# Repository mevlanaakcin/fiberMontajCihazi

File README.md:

# fiberMontajCihazi
Uçak Elektronik sanayisinde fiberoptik kabloların soketlenmesi için geliştirilen cihaz<br>
<h3>PCB Tasarımı</h3><br>
Elektronik devre şeması ve PCB board tasarımı Eagle de tasarlandı.<br>

<h3>Gömülü Yazılım</h3><br>
Bir masaüstü haberleşme ile iletişim kurabilmesi için Serial Haberleşme kullanıldı.<br>
LCD ekran için I2C kullanıldı.<br>
Shift Register Entegrelerini sürebilmek için SPI kullanıldı.<br>

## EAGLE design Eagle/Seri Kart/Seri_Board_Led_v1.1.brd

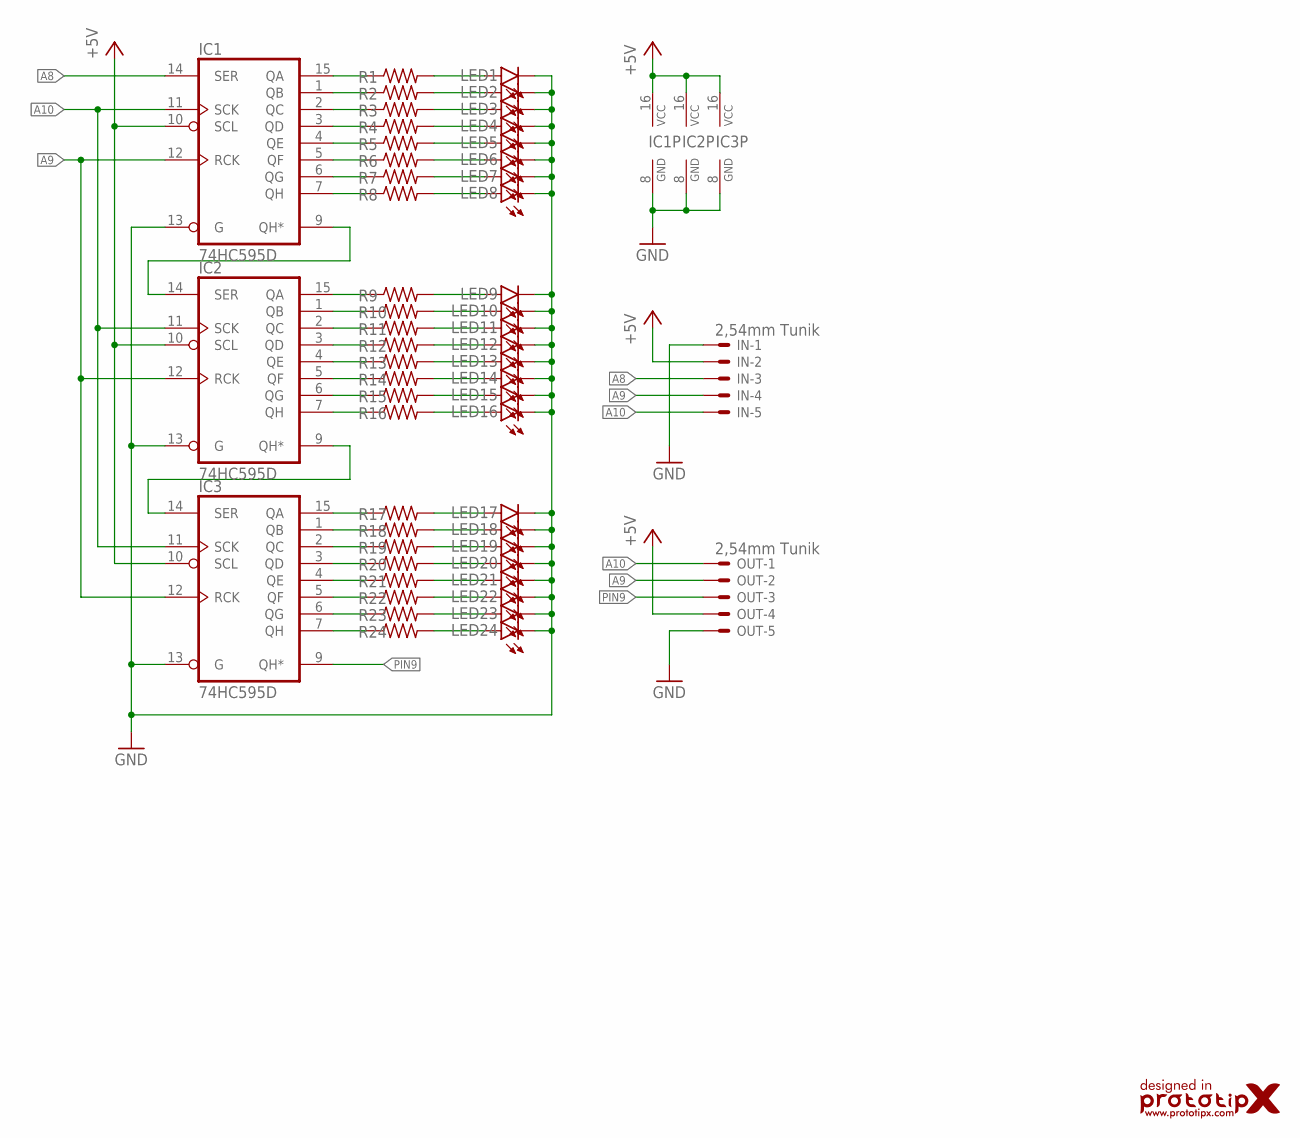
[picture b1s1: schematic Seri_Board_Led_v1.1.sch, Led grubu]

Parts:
IC1, IC2, IC3: 74HC595D; SO16
IN: 2,54mm Tunik; 70543-05
LED1, LED2, LED3, LED4, LED5, LED6, LED7, LED8, LED9, LED10, LED11, LED12, LED13, LED14, LED15, LED16, LED17, LED18, LED19, LED20, LED21, LED22, LED23, LED24: RED; LED3MM
LOGO1: PROTOTIPXDESIGN2; PROTOTIPX_DESING_15MM
OUT: 2,54mm Tunik; 70543-05
R1, R2, R3, R4, R5, R6, R7, R8, R9, R10, R11, R12, R13, R14, R15, R16, R17, R18, R19, R20, R21, R22, R23, R24: 220R; R0805

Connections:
+5V: IC1.10 (SCL), IC1.16 (VCC), IC2.10 (SCL), IC2.16 (VCC), IC3.10 (SCL), IC3.16 (VCC), IN.2, OUT.4
A8: IC1.14 (SER), IN.3
A9: IC1.12 (RCK), IC2.12 (RCK), IC3.12 (RCK), IN.4, OUT.2
A10: IC1.11 (SCK), IC2.11 (SCK), IC3.11 (SCK), IN.5, OUT.1
GND: IC1.8 (GND), IC1.13 (G), IC2.8 (GND), IC2.13 (G), IC3.8 (GND), IC3.13 (G), IN.1, LED1.K (C), LED2.K (C), LED3.K (C), LED4.K (C), LED5.K (C), LED6.K (C), LED7.K (C), LED8.K (C), LED9.K (C), LED10.K (C), LED11.K (C), LED12.K (C), LED13.K (C), LED14.K (C), LED15.K (C), LED16.K (C), LED17.K (C), LED18.K (C), LED19.K (C), LED20.K (C), LED21.K (C), LED22.K (C), LED23.K (C), LED24.K (C), OUT.5
unnamed: LED1.A, R1.2
unnamed: IC1.15 (QA), R1.1
unnamed: IC1.1 (QB), R2.1
unnamed: LED2.A, R2.2
unnamed: IC1.2 (QC), R3.1
unnamed: LED3.A, R3.2
unnamed: IC1.3 (QD), R4.1
unnamed: LED4.A, R4.2
unnamed: IC1.4 (QE), R5.1
unnamed: LED5.A, R5.2
unnamed: IC1.5 (QF), R6.1
unnamed: LED6.A, R6.2
unnamed: IC1.6 (QG), R7.1
unnamed: LED7.A, R7.2
unnamed: IC1.7 (QH), R8.1
unnamed: LED8.A, R8.2
unnamed: IC2.15 (QA), R9.1
unnamed: LED9.A, R9.2
unnamed: IC2.1 (QB), R10.1
unnamed: LED10.A, R10.2
unnamed: IC2.2 (QC), R11.1
unnamed: LED11.A, R11.2
unnamed: IC2.3 (QD), R12.1
unnamed: LED12.A, R12.2
unnamed: IC2.4 (QE), R13.1
unnamed: LED13.A, R13.2
unnamed: IC2.5 (QF), R14.1
unnamed: LED14.A, R14.2
unnamed: IC2.6 (QG), R15.1
unnamed: LED15.A, R15.2
unnamed: IC2.7 (QH), R16.1
unnamed: LED16.A, R16.2
unnamed: IC3.15 (QA), R17.1
unnamed: LED17.A, R17.2
unnamed: IC3.1 (QB), R18.1
unnamed: LED18.A, R18.2
unnamed: IC3.2 (QC), R19.1
unnamed: LED19.A, R19.2
unnamed: IC3.3 (QD), R20.1
unnamed: LED20.A, R20.2
unnamed: IC3.4 (QE), R21.1
unnamed: LED21.A, R21.2
unnamed: IC3.5 (QF), R22.1
unnamed: LED22.A, R22.2
unnamed: IC3.6 (QG), R23.1
unnamed: LED23.A, R23.2
unnamed: IC3.7 (QH), R24.1
unnamed: LED24.A, R24.2
unnamed: IC1.9 (QH*), IC2.14 (SER)
unnamed: IC2.9 (QH*), IC3.14 (SER)
PIN9: IC3.9 (QH*), OUT.3

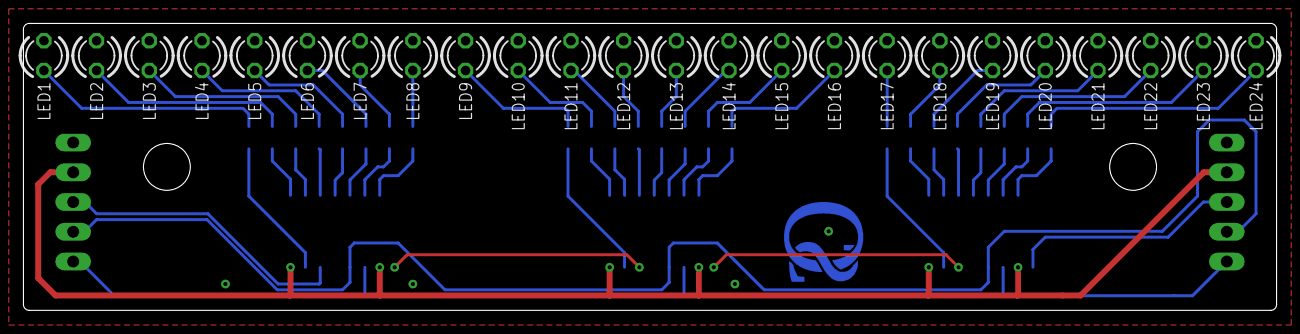
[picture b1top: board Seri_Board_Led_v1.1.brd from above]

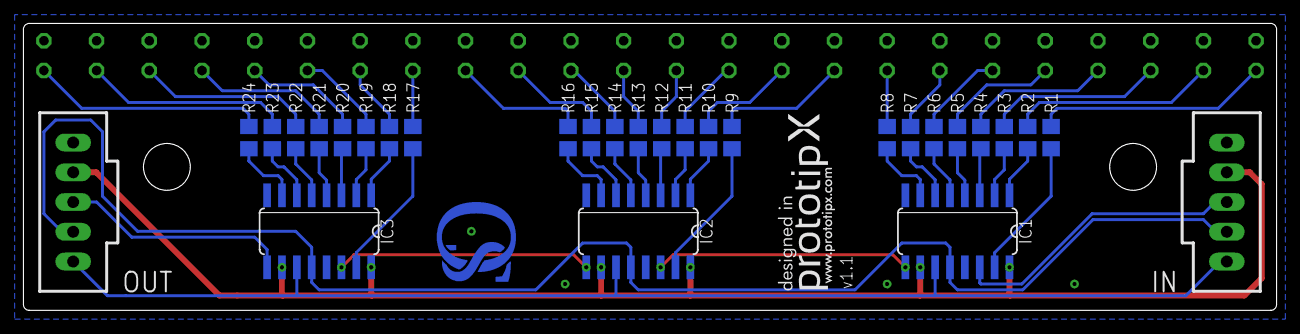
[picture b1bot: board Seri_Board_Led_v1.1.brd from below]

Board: 2 copper layers, 107.0 x 24.5 mm, 54 parts (30 on the bottom side), 56 nets.

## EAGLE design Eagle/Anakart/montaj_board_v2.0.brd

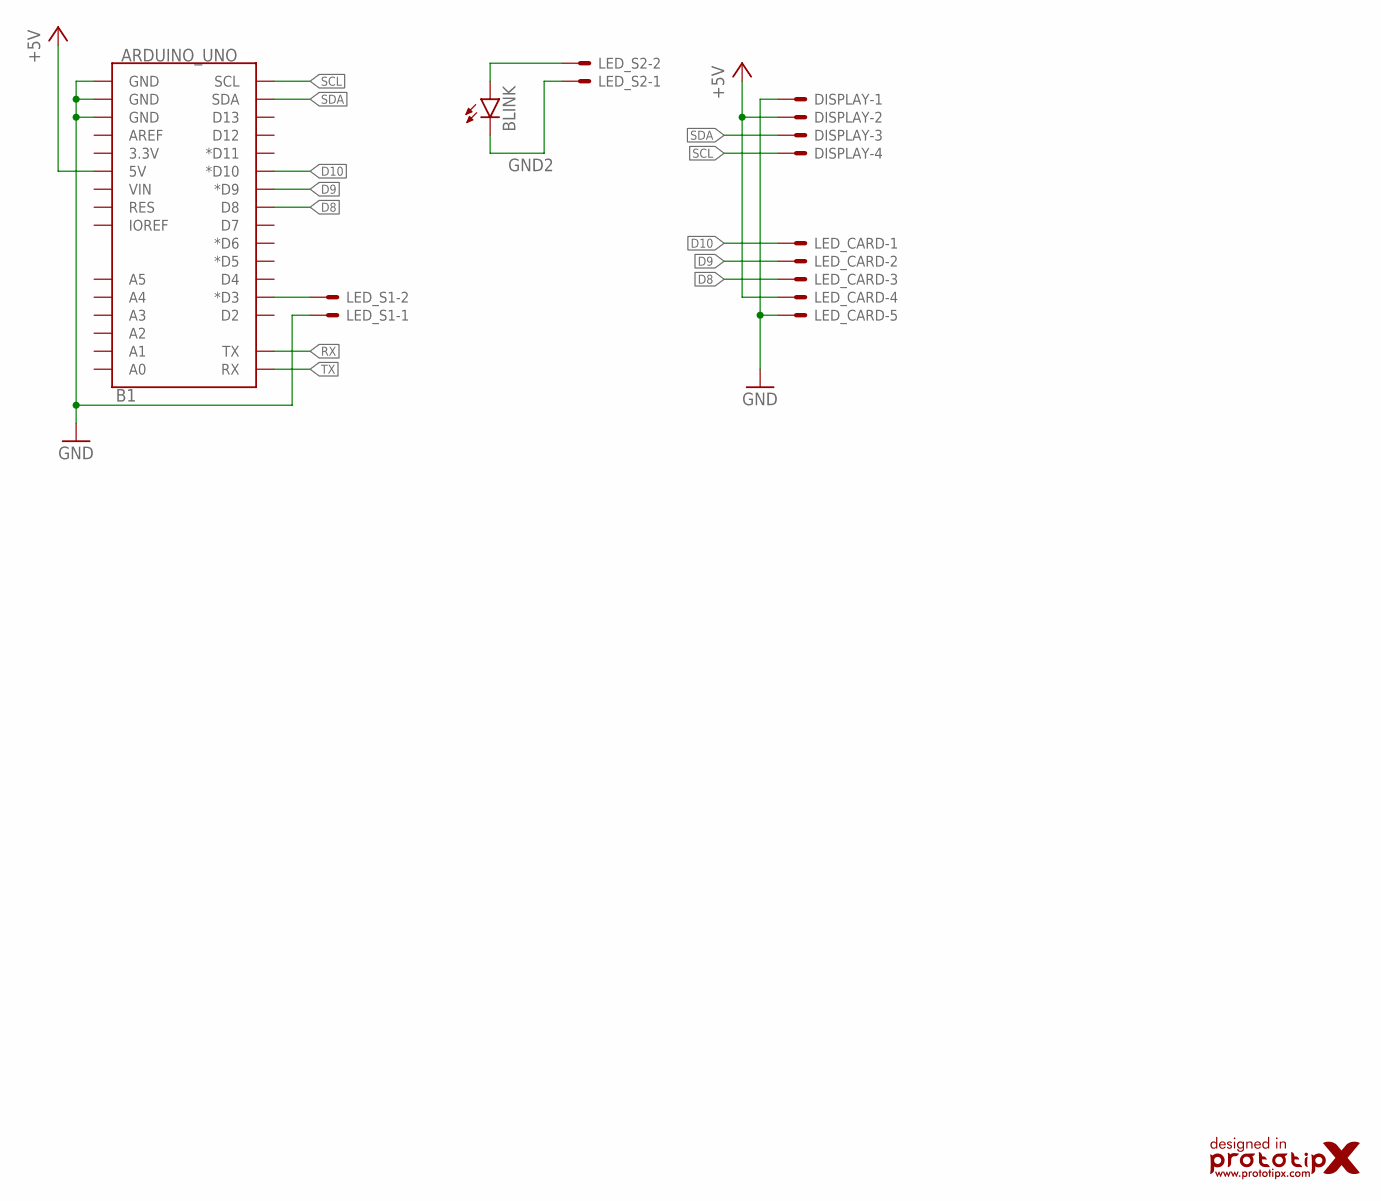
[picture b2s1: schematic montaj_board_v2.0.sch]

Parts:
B1: ARDUINO_UNO; UNO_R3_SHIELD
BLINK: LED3MM
DISPLAY: C-GRID-04-70543; 70543-04
LED_CARD: C-GRID-05-70543; 70543-05
LED_S1, LED_S2: C-GRID-02-70543; 70543-02
LOGO1: PROTOTIPXDESIGN; PROTOTIPX_DESING_20MM

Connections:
+5V: B1.5V, DISPLAY.2, LED_CARD.4
D8: B1.D8, LED_CARD.3
D9: B1.D9 (*D9), LED_CARD.2
D10: B1.D10 (*D10), LED_CARD.1
GND: B1.GND@0 (GND), B1.GND@1 (GND), B1.GND@2 (GND), DISPLAY.1, LED_CARD.5, LED_S1.1
GND2: BLINK.K (C), LED_S2.1
unnamed: B1.D3 (*D3), LED_S1.2
unnamed: BLINK.A, LED_S2.2
RX: B1.TX
SCL: B1.SCL, DISPLAY.4
SDA: B1.SDA, DISPLAY.3
TX: B1.RX

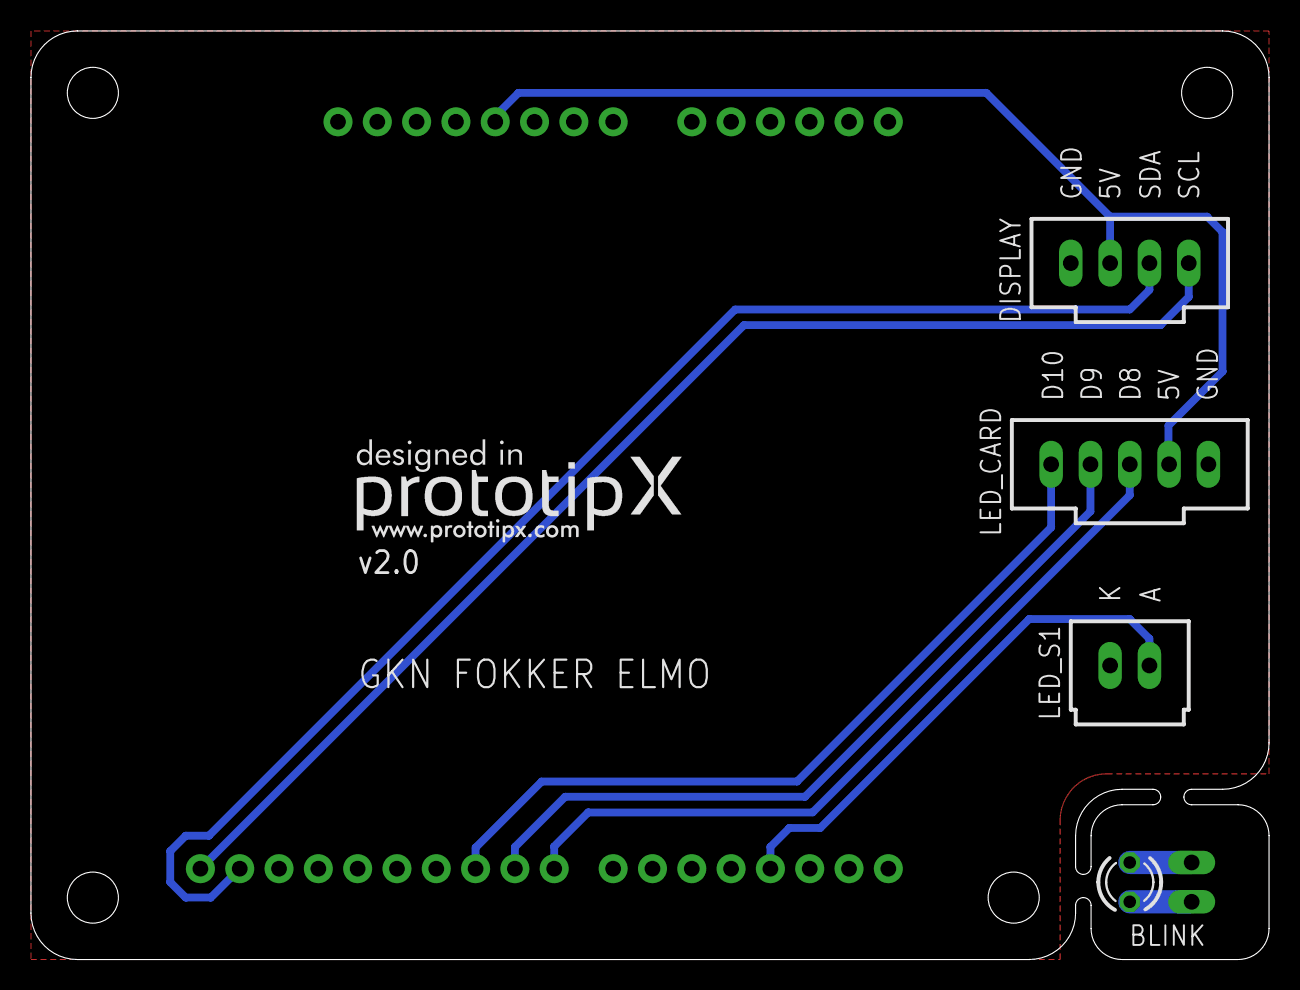
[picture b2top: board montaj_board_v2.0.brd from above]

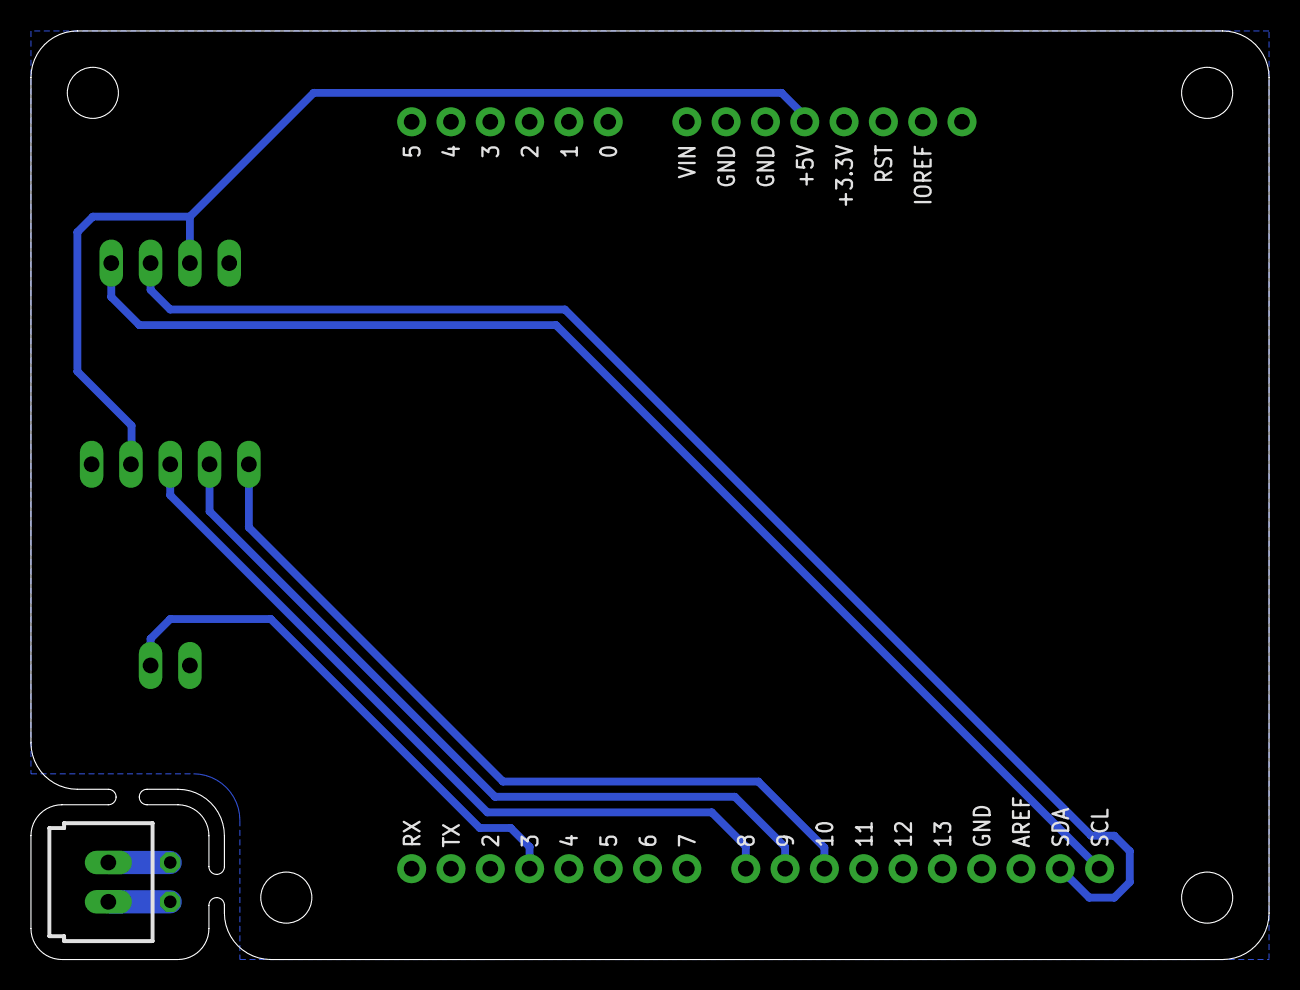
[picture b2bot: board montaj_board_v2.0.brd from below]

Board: 2 copper layers, 80.0 x 60.0 mm, 7 parts (2 on the bottom side), 10 nets.

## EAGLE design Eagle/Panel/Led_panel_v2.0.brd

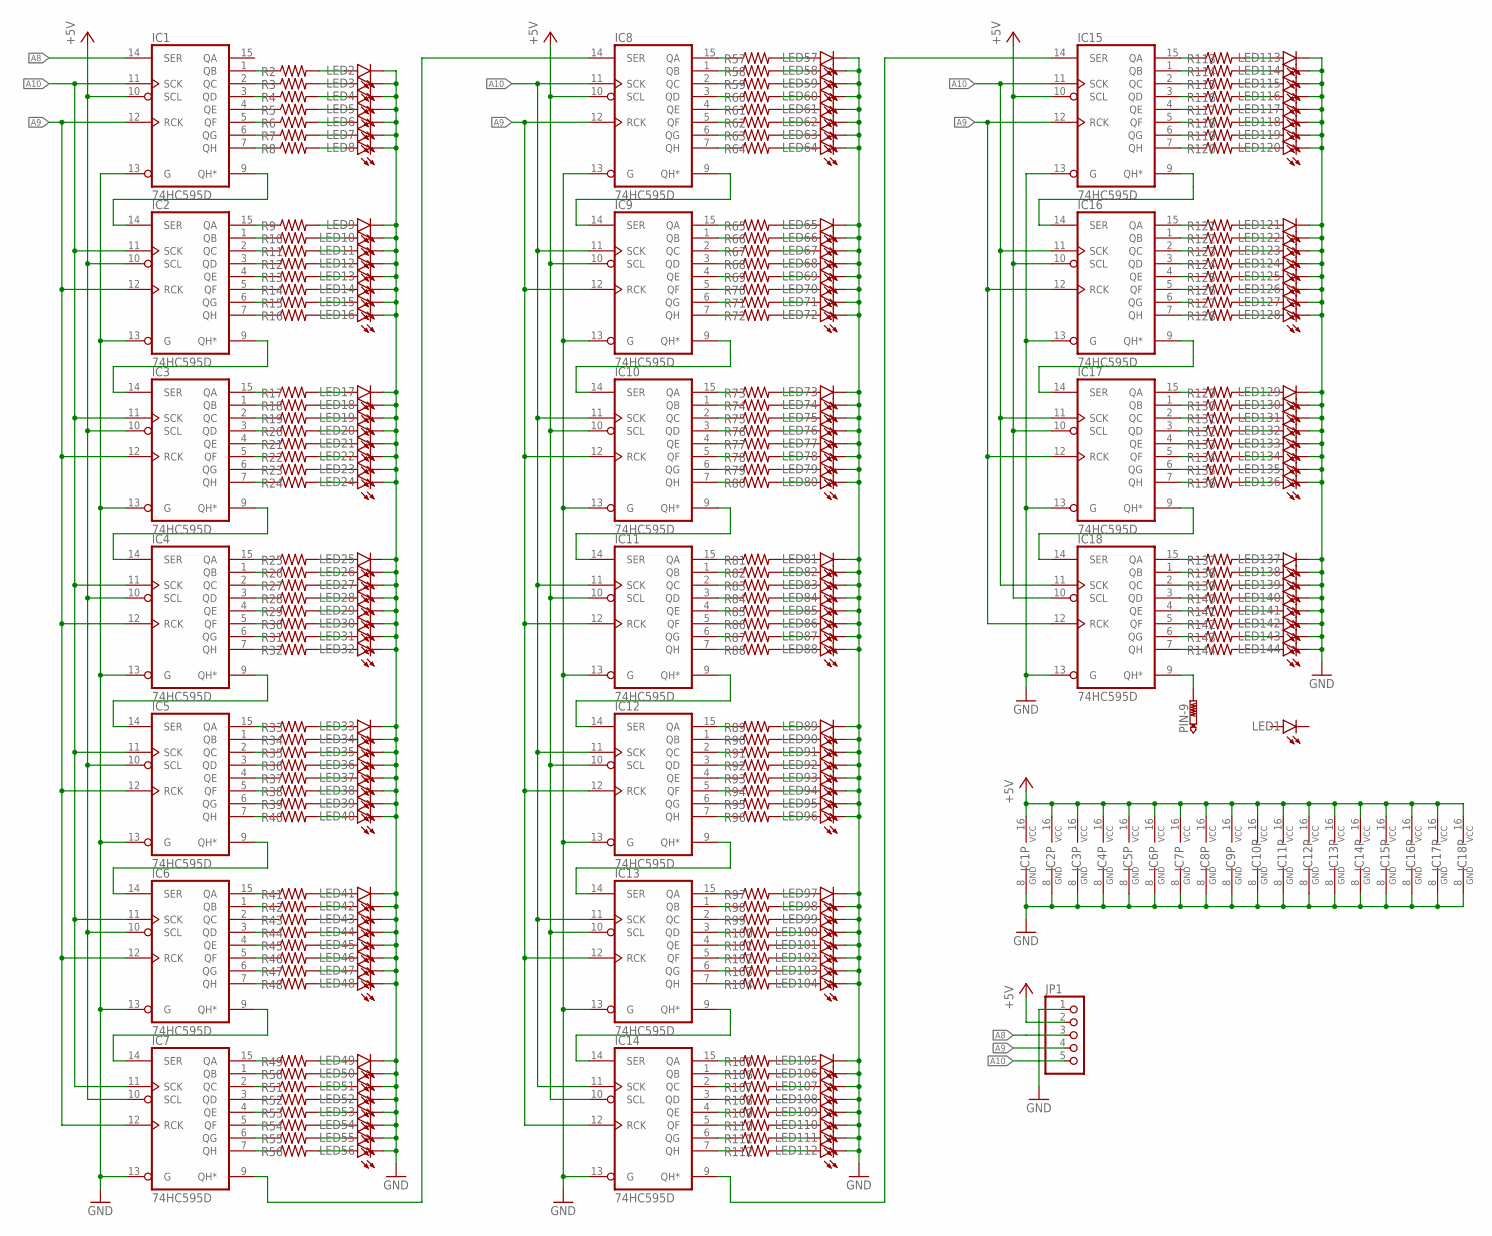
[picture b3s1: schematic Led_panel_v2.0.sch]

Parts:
IC1, IC2, IC3, IC4, IC5, IC6, IC7, IC8, IC9, IC10, IC11, IC12, IC13, IC14, IC15, IC16, IC17, IC18: 74HC595D; SO16
JP1: PINHD-1X5; 1X05
LED1, LED2, LED3, LED4, LED5, LED6, LED7, LED8, LED9, LED10, LED11, LED12, LED13, LED14, LED15, LED16, LED17, LED18, LED19, LED20, LED21, LED22, LED23, LED24, LED25, LED26, LED27, LED28, LED29, LED30, LED31, LED32, LED33, LED34, LED35, LED36, LED37, LED38, LED39, LED40, LED41, LED42, LED43, LED44, LED45, LED46, LED47, LED48, LED49, LED50, LED51, LED52, LED53, LED54, LED55, LED56, LED57, LED58, LED59, LED60, LED61, LED62, LED63, LED64, LED65, LED66, LED67, LED68, LED69, LED70, LED71, LED72, LED73, LED74, LED75, LED76, LED77, LED78, LED79, LED80, LED81, LED82, LED83, LED84, LED85, LED86, LED87, LED88, LED89, LED90, LED91, LED92, LED93, LED94, LED95, LED96, LED97, LED98, LED99, LED100, LED101, LED102, LED103, LED104, LED105, LED106, LED107, LED108, LED109, LED110, LED111, LED112, LED113, LED114, LED115, LED116, LED117, LED118, LED119, LED120, LED121, LED122, LED123, LED124, LED125, LED126, LED127, LED128, LED129, LED130, LED131, LED132, LED133, LED134, LED135, LED136, LED137, LED138, LED139, LED140, LED141, LED142, LED143, LED144: LED3MM
PIN-9: PTR1TP20R; TP20R
R2, R3, R4, R5, R6, R7, R8, R9, R10, R11, R12, R13, R14, R15, R16, R17, R18, R19, R20, R21, R22, R23, R24, R25, R26, R27, R28, R29, R30, R31, R32, R33, R34, R35, R36, R37, R38, R39, R40, R41, R42, R43, R44, R45, R46, R47, R48, R49, R50, R51, R52, R53, R54, R55, R56, R57, R58, R59, R60, R61, R62, R63, R64, R65, R66, R67, R68, R69, R70, R71, R72, R73, R74, R75, R76, R77, R78, R79, R80, R81, R82, R83, R84, R85, R86, R87, R88, R89, R90, R91, R92, R93, R94, R95, R96, R97, R98, R99, R100, R101, R102, R103, R104, R105, R106, R107, R108, R109, R110, R111, R112, R113, R114, R115, R116, R117, R118, R119, R120, R121, R122, R123, R124, R125, R126, R127, R128, R129, R130, R131, R132, R133, R134, R135, R136, R137, R138, R139, R140, R141, R142, R143, R144: 120R; R0805

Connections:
+5V: IC1.10 (SCL), IC1.16 (VCC), IC2.10 (SCL), IC2.16 (VCC), IC3.10 (SCL), IC3.16 (VCC), IC4.10 (SCL), IC4.16 (VCC), IC5.10 (SCL), IC5.16 (VCC), IC6.10 (SCL), IC6.16 (VCC), IC7.10 (SCL), IC7.16 (VCC), IC8.10 (SCL), IC8.16 (VCC), IC9.10 (SCL), IC9.16 (VCC), IC10.10 (SCL), IC10.16 (VCC), IC11.10 (SCL), IC11.16 (VCC), IC12.10 (SCL), IC12.16 (VCC), IC13.10 (SCL), IC13.16 (VCC), IC14.10 (SCL), IC14.16 (VCC), IC15.10 (SCL), IC15.16 (VCC), IC16.10 (SCL), IC16.16 (VCC), IC17.10 (SCL), IC17.16 (VCC), IC18.10 (SCL), IC18.16 (VCC), JP1.2
A8: IC1.14 (SER), JP1.3
A9: IC1.12 (RCK), IC2.12 (RCK), IC3.12 (RCK), IC4.12 (RCK), IC5.12 (RCK), IC6.12 (RCK), IC7.12 (RCK), IC8.12 (RCK), IC9.12 (RCK), IC10.12 (RCK), IC11.12 (RCK), IC12.12 (RCK), IC13.12 (RCK), IC14.12 (RCK), IC15.12 (RCK), IC16.12 (RCK), IC17.12 (RCK), IC18.12 (RCK), JP1.4
A10: IC1.11 (SCK), IC2.11 (SCK), IC3.11 (SCK), IC4.11 (SCK), IC5.11 (SCK), IC6.11 (SCK), IC7.11 (SCK), IC8.11 (SCK), IC9.11 (SCK), IC10.11 (SCK), IC11.11 (SCK), IC12.11 (SCK), IC13.11 (SCK), IC14.11 (SCK), IC15.11 (SCK), IC16.11 (SCK), IC17.11 (SCK), IC18.11 (SCK), JP1.5
GND: IC1.8 (GND), IC1.13 (G), IC2.8 (GND), IC2.13 (G), IC3.8 (GND), IC3.13 (G), IC4.8 (GND), IC4.13 (G), IC5.8 (GND), IC5.13 (G), IC6.8 (GND), IC6.13 (G), IC7.8 (GND), IC7.13 (G), IC8.8 (GND), IC8.13 (G), IC9.8 (GND), IC9.13 (G), IC10.8 (GND), IC10.13 (G), IC11.8 (GND), IC11.13 (G), IC12.8 (GND), IC12.13 (G), IC13.8 (GND), IC13.13 (G), IC14.8 (GND), IC14.13 (G), IC15.8 (GND), IC15.13 (G), IC16.8 (GND), IC16.13 (G), IC17.8 (GND), IC17.13 (G), IC18.8 (GND), IC18.13 (G), JP1.1, LED2.K (C), LED3.K (C), LED4.K (C), LED5.K (C), LED6.K (C), LED7.K (C), LED8.K (C), LED9.K (C), LED10.K (C), LED11.K (C), LED12.K (C), LED13.K (C), LED14.K (C), LED15.K (C), LED16.K (C), LED17.K (C), LED18.K (C), LED19.K (C), LED20.K (C), LED21.K (C), LED22.K (C), LED23.K (C), LED24.K (C), LED25.K (C), LED26.K (C), LED27.K (C), LED28.K (C), LED29.K (C), LED30.K (C), LED31.K (C), LED32.K (C), LED33.K (C), LED34.K (C), LED35.K (C), LED36.K (C), LED37.K (C), LED38.K (C), LED39.K (C), LED40.K (C), LED41.K (C), LED42.K (C), LED43.K (C), LED44.K (C), LED45.K (C), LED46.K (C), LED47.K (C), LED48.K (C), LED49.K (C), LED50.K (C), LED51.K (C), LED52.K (C), LED53.K (C), LED54.K (C), LED55.K (C), LED56.K (C), LED57.K (C), LED58.K (C), LED59.K (C), LED60.K (C), LED61.K (C), LED62.K (C), LED63.K (C), LED64.K (C), LED65.K (C), LED66.K (C), LED67.K (C), LED68.K (C), LED69.K (C), LED70.K (C), LED71.K (C), LED72.K (C), LED73.K (C), LED74.K (C), LED75.K (C), LED76.K (C), LED77.K (C), LED78.K (C), LED79.K (C), LED80.K (C), LED81.K (C), LED82.K (C), LED83.K (C), LED84.K (C), LED85.K (C), LED86.K (C), LED87.K (C), LED88.K (C), LED89.K (C), LED90.K (C), LED91.K (C), LED92.K (C), LED93.K (C), LED94.K (C), LED95.K (C), LED96.K (C), LED97.K (C), LED98.K (C), LED99.K (C), LED100.K (C), LED101.K (C), LED102.K (C), LED103.K (C), LED104.K (C), LED105.K (C), LED106.K (C), LED107.K (C), LED108.K (C), LED109.K (C), LED110.K (C), LED111.K (C), LED112.K (C), LED113.K (C), LED114.K (C), LED115.K (C), LED116.K (C), LED117.K (C), LED118.K (C), LED119.K (C), LED120.K (C), LED121.K (C), LED122.K (C), LED123.K (C), LED124.K (C), LED125.K (C), LED126.K (C), LED127.K (C), LED128.K (C), LED129.K (C), LED130.K (C), LED131.K (C), LED132.K (C), LED133.K (C), LED134.K (C), LED135.K (C), LED136.K (C), LED137.K (C), LED138.K (C), LED139.K (C), LED140.K (C), LED141.K (C), LED142.K (C), LED143.K (C), LED144.K (C)
unnamed: IC18.9 (QH*), PIN-9.TP
unnamed: IC1.1 (QB), R2.1
unnamed: LED2.A, R2.2
unnamed: IC1.2 (QC), R3.1
unnamed: LED3.A, R3.2
unnamed: IC1.3 (QD), R4.1
unnamed: LED4.A, R4.2
unnamed: IC1.4 (QE), R5.1
unnamed: LED5.A, R5.2
unnamed: IC1.5 (QF), R6.1
unnamed: LED6.A, R6.2
unnamed: IC1.6 (QG), R7.1
unnamed: LED7.A, R7.2
unnamed: IC1.7 (QH), R8.1
unnamed: LED8.A, R8.2
unnamed: IC2.15 (QA), R9.1
unnamed: LED9.A, R9.2
unnamed: IC2.1 (QB), R10.1
unnamed: LED10.A, R10.2
unnamed: IC2.2 (QC), R11.1
unnamed: LED11.A, R11.2
unnamed: IC2.3 (QD), R12.1
unnamed: LED12.A, R12.2
unnamed: IC2.4 (QE), R13.1
unnamed: LED13.A, R13.2
unnamed: IC2.5 (QF), R14.1
unnamed: LED14.A, R14.2
unnamed: IC2.6 (QG), R15.1
unnamed: LED15.A, R15.2
unnamed: IC2.7 (QH), R16.1
unnamed: LED16.A, R16.2
unnamed: IC3.15 (QA), R17.1
unnamed: LED17.A, R17.2
unnamed: IC3.1 (QB), R18.1
unnamed: LED18.A, R18.2
unnamed: IC3.2 (QC), R19.1
unnamed: LED19.A, R19.2
unnamed: IC3.3 (QD), R20.1
unnamed: LED20.A, R20.2
unnamed: IC3.4 (QE), R21.1
unnamed: LED21.A, R21.2
unnamed: IC3.5 (QF), R22.1
unnamed: LED22.A, R22.2
unnamed: IC3.6 (QG), R23.1
unnamed: LED23.A, R23.2
unnamed: IC3.7 (QH), R24.1
unnamed: LED24.A, R24.2
unnamed: IC4.15 (QA), R25.1
unnamed: LED25.A, R25.2
unnamed: IC4.1 (QB), R26.1
unnamed: LED26.A, R26.2
unnamed: IC4.2 (QC), R27.1
unnamed: LED27.A, R27.2
unnamed: IC4.3 (QD), R28.1
unnamed: LED28.A, R28.2
unnamed: IC4.4 (QE), R29.1
unnamed: LED29.A, R29.2
unnamed: IC4.5 (QF), R30.1
unnamed: LED30.A, R30.2
unnamed: IC4.6 (QG), R31.1
unnamed: LED31.A, R31.2
unnamed: IC4.7 (QH), R32.1
unnamed: LED32.A, R32.2
unnamed: IC5.15 (QA), R33.1
unnamed: LED33.A, R33.2
unnamed: IC5.1 (QB), R34.1
unnamed: LED34.A, R34.2
unnamed: IC5.2 (QC), R35.1
unnamed: LED35.A, R35.2
unnamed: IC5.3 (QD), R36.1
unnamed: LED36.A, R36.2
unnamed: IC5.4 (QE), R37.1
unnamed: LED37.A, R37.2
unnamed: IC5.5 (QF), R38.1
unnamed: LED38.A, R38.2
unnamed: IC5.6 (QG), R39.1
unnamed: LED39.A, R39.2
unnamed: IC5.7 (QH), R40.1
unnamed: LED40.A, R40.2
unnamed: IC6.15 (QA), R41.1
unnamed: LED41.A, R41.2
unnamed: IC6.1 (QB), R42.1
unnamed: LED42.A, R42.2
unnamed: IC6.2 (QC), R43.1
unnamed: LED43.A, R43.2
unnamed: IC6.3 (QD), R44.1
unnamed: LED44.A, R44.2
unnamed: IC6.4 (QE), R45.1
unnamed: LED45.A, R45.2
unnamed: IC6.5 (QF), R46.1
unnamed: LED46.A, R46.2
unnamed: IC6.6 (QG), R47.1
unnamed: LED47.A, R47.2
unnamed: IC6.7 (QH), R48.1
unnamed: LED48.A, R48.2
unnamed: IC7.15 (QA), R49.1
unnamed: LED49.A, R49.2
unnamed: IC7.1 (QB), R50.1
unnamed: LED50.A, R50.2
unnamed: IC7.2 (QC), R51.1
unnamed: LED51.A, R51.2
unnamed: IC7.3 (QD), R52.1
unnamed: LED52.A, R52.2
unnamed: IC7.4 (QE), R53.1
unnamed: LED53.A, R53.2
unnamed: IC7.5 (QF), R54.1
unnamed: LED54.A, R54.2
unnamed: IC7.6 (QG), R55.1
unnamed: LED55.A, R55.2
unnamed: IC7.7 (QH), R56.1
unnamed: LED56.A, R56.2
unnamed: IC8.15 (QA), R57.1
unnamed: LED57.A, R57.2
unnamed: IC8.1 (QB), R58.1
unnamed: LED58.A, R58.2
unnamed: IC8.2 (QC), R59.1
unnamed: LED59.A, R59.2
unnamed: IC8.3 (QD), R60.1
unnamed: LED60.A, R60.2
unnamed: IC8.4 (QE), R61.1
unnamed: LED61.A, R61.2
unnamed: IC8.5 (QF), R62.1
unnamed: LED62.A, R62.2
unnamed: IC8.6 (QG), R63.1
unnamed: LED63.A, R63.2
unnamed: IC8.7 (QH), R64.1
unnamed: LED64.A, R64.2
unnamed: IC9.15 (QA), R65.1
unnamed: LED65.A, R65.2
unnamed: IC9.1 (QB), R66.1
unnamed: LED66.A, R66.2
unnamed: IC9.2 (QC), R67.1
unnamed: LED67.A, R67.2
unnamed: IC9.3 (QD), R68.1
unnamed: LED68.A, R68.2
unnamed: IC9.4 (QE), R69.1
unnamed: LED69.A, R69.2
unnamed: IC9.5 (QF), R70.1
unnamed: LED70.A, R70.2
unnamed: IC9.6 (QG), R71.1
unnamed: LED71.A, R71.2
unnamed: IC9.7 (QH), R72.1
unnamed: LED72.A, R72.2
unnamed: IC10.15 (QA), R73.1
unnamed: LED73.A, R73.2
unnamed: IC10.1 (QB), R74.1
unnamed: LED74.A, R74.2
unnamed: IC10.2 (QC), R75.1
unnamed: LED75.A, R75.2
unnamed: IC10.3 (QD), R76.1
unnamed: LED76.A, R76.2
unnamed: IC10.4 (QE), R77.1
unnamed: LED77.A, R77.2
unnamed: IC10.5 (QF), R78.1
unnamed: LED78.A, R78.2
unnamed: IC10.6 (QG), R79.1
unnamed: LED79.A, R79.2
unnamed: IC10.7 (QH), R80.1
unnamed: LED80.A, R80.2
unnamed: IC11.15 (QA), R81.1
unnamed: LED81.A, R81.2
unnamed: IC11.1 (QB), R82.1
unnamed: LED82.A, R82.2
unnamed: IC11.2 (QC), R83.1
unnamed: LED83.A, R83.2
unnamed: IC11.3 (QD), R84.1
unnamed: LED84.A, R84.2
unnamed: IC11.4 (QE), R85.1
unnamed: LED85.A, R85.2
unnamed: IC11.5 (QF), R86.1
unnamed: LED86.A, R86.2
unnamed: IC11.6 (QG), R87.1
unnamed: LED87.A, R87.2
unnamed: IC11.7 (QH), R88.1
unnamed: LED88.A, R88.2
unnamed: IC12.15 (QA), R89.1
unnamed: LED89.A, R89.2
unnamed: IC12.1 (QB), R90.1
unnamed: LED90.A, R90.2
unnamed: IC12.2 (QC), R91.1
unnamed: LED91.A, R91.2
unnamed: IC12.3 (QD), R92.1
unnamed: LED92.A, R92.2
unnamed: IC12.4 (QE), R93.1
unnamed: LED93.A, R93.2
unnamed: IC12.5 (QF), R94.1
unnamed: LED94.A, R94.2
unnamed: IC12.6 (QG), R95.1
unnamed: LED95.A, R95.2
unnamed: IC12.7 (QH), R96.1
unnamed: LED96.A, R96.2
unnamed: IC13.15 (QA), R97.1
unnamed: LED97.A, R97.2
unnamed: IC13.1 (QB), R98.1
unnamed: LED98.A, R98.2
unnamed: IC13.2 (QC), R99.1
unnamed: LED99.A, R99.2
unnamed: IC13.3 (QD), R100.1
unnamed: LED100.A, R100.2
unnamed: IC13.4 (QE), R101.1
unnamed: LED101.A, R101.2
unnamed: IC13.5 (QF), R102.1
unnamed: LED102.A, R102.2
unnamed: IC13.6 (QG), R103.1
unnamed: LED103.A, R103.2
unnamed: IC13.7 (QH), R104.1
unnamed: LED104.A, R104.2
unnamed: IC14.15 (QA), R105.1
unnamed: LED105.A, R105.2
unnamed: IC14.1 (QB), R106.1
unnamed: LED106.A, R106.2
unnamed: IC14.2 (QC), R107.1
unnamed: LED107.A, R107.2
unnamed: IC14.3 (QD), R108.1
unnamed: LED108.A, R108.2
unnamed: IC14.4 (QE), R109.1
unnamed: LED109.A, R109.2
unnamed: IC14.5 (QF), R110.1
unnamed: LED110.A, R110.2
unnamed: IC14.6 (QG), R111.1
unnamed: LED111.A, R111.2
unnamed: IC14.7 (QH), R112.1
unnamed: LED112.A, R112.2
unnamed: IC15.15 (QA), R113.1
unnamed: LED113.A, R113.2
unnamed: IC15.1 (QB), R114.1
unnamed: LED114.A, R114.2
unnamed: IC15.2 (QC), R115.1
unnamed: LED115.A, R115.2
unnamed: IC15.3 (QD), R116.1
unnamed: LED116.A, R116.2
unnamed: IC15.4 (QE), R117.1
unnamed: LED117.A, R117.2
unnamed: IC15.5 (QF), R118.1
unnamed: LED118.A, R118.2
unnamed: IC15.6 (QG), R119.1
unnamed: LED119.A, R119.2
unnamed: IC15.7 (QH), R120.1
unnamed: LED120.A, R120.2
unnamed: IC16.15 (QA), R121.1
unnamed: LED121.A, R121.2
unnamed: IC16.1 (QB), R122.1
unnamed: LED122.A, R122.2
unnamed: IC16.2 (QC), R123.1
unnamed: LED123.A, R123.2
unnamed: IC16.3 (QD), R124.1
unnamed: LED124.A, R124.2
unnamed: IC16.4 (QE), R125.1
unnamed: LED125.A, R125.2
unnamed: IC16.5 (QF), R126.1
unnamed: LED126.A, R126.2
unnamed: IC16.6 (QG), R127.1
unnamed: LED127.A, R127.2
unnamed: IC16.7 (QH), R128.1
unnamed: LED128.A, R128.2
unnamed: IC17.15 (QA), R129.1
unnamed: LED129.A, R129.2
unnamed: IC17.1 (QB), R130.1
unnamed: LED130.A, R130.2
unnamed: IC17.2 (QC), R131.1
unnamed: LED131.A, R131.2
unnamed: IC17.3 (QD), R132.1
unnamed: LED132.A, R132.2
unnamed: IC17.4 (QE), R133.1
unnamed: LED133.A, R133.2
unnamed: IC17.5 (QF), R134.1
unnamed: LED134.A, R134.2
unnamed: IC17.6 (QG), R135.1
unnamed: LED135.A, R135.2
unnamed: IC17.7 (QH), R136.1
unnamed: LED136.A, R136.2
unnamed: IC18.15 (QA), R137.1
unnamed: LED137.A, R137.2
unnamed: IC18.1 (QB), R138.1
unnamed: LED138.A, R138.2
unnamed: IC18.2 (QC), R139.1
unnamed: LED139.A, R139.2
unnamed: IC18.3 (QD), R140.1
unnamed: LED140.A, R140.2
unnamed: IC18.4 (QE), R141.1
unnamed: LED141.A, R141.2
unnamed: IC18.5 (QF), R142.1
unnamed: LED142.A, R142.2
unnamed: IC18.6 (QG), R143.1
unnamed: LED143.A, R143.2
unnamed: IC18.7 (QH), R144.1
unnamed: LED144.A, R144.2
unnamed: IC1.9 (QH*), IC2.14 (SER)
unnamed: IC2.9 (QH*), IC3.14 (SER)
unnamed: IC3.9 (QH*), IC4.14 (SER)
unnamed: IC4.9 (QH*), IC5.14 (SER)
unnamed: IC5.9 (QH*), IC6.14 (SER)
unnamed: IC6.9 (QH*), IC7.14 (SER)
unnamed: IC7.9 (QH*), IC8.14 (SER)
unnamed: IC8.9 (QH*), IC9.14 (SER)
unnamed: IC9.9 (QH*), IC10.14 (SER)
unnamed: IC10.9 (QH*), IC11.14 (SER)
unnamed: IC11.9 (QH*), IC12.14 (SER)
unnamed: IC12.9 (QH*), IC13.14 (SER)
unnamed: IC13.9 (QH*), IC14.14 (SER)
unnamed: IC14.9 (QH*), IC15.14 (SER)
unnamed: IC15.9 (QH*), IC16.14 (SER)
unnamed: IC16.9 (QH*), IC17.14 (SER)
unnamed: IC17.9 (QH*), IC18.14 (SER)

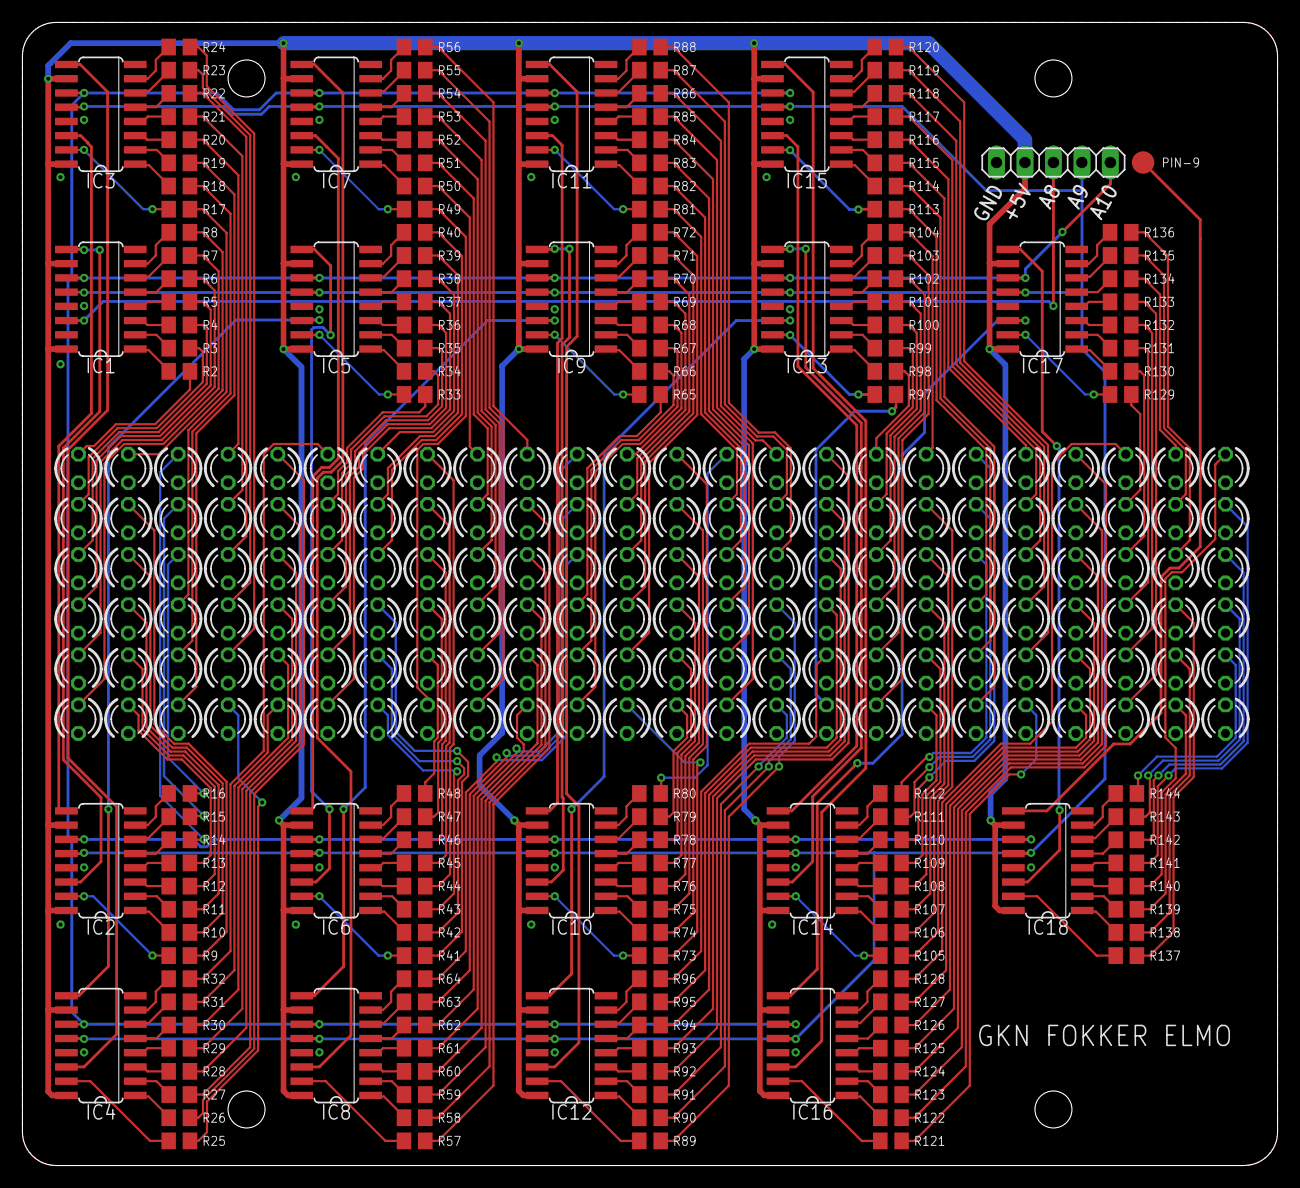
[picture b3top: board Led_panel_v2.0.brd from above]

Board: 2 copper layers, 112.0 x 102.0 mm, 307 parts (0 on the bottom side), 309 nets.

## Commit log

2022-11-18 Commit Test
2022-11-18 Test Commit

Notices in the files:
parts and their libraries:
SparkFun-Boards: Licensing: Creative Commons ShareAlike 4.0 International - https://creativecommons.org/licenses/by-sa/4.0
